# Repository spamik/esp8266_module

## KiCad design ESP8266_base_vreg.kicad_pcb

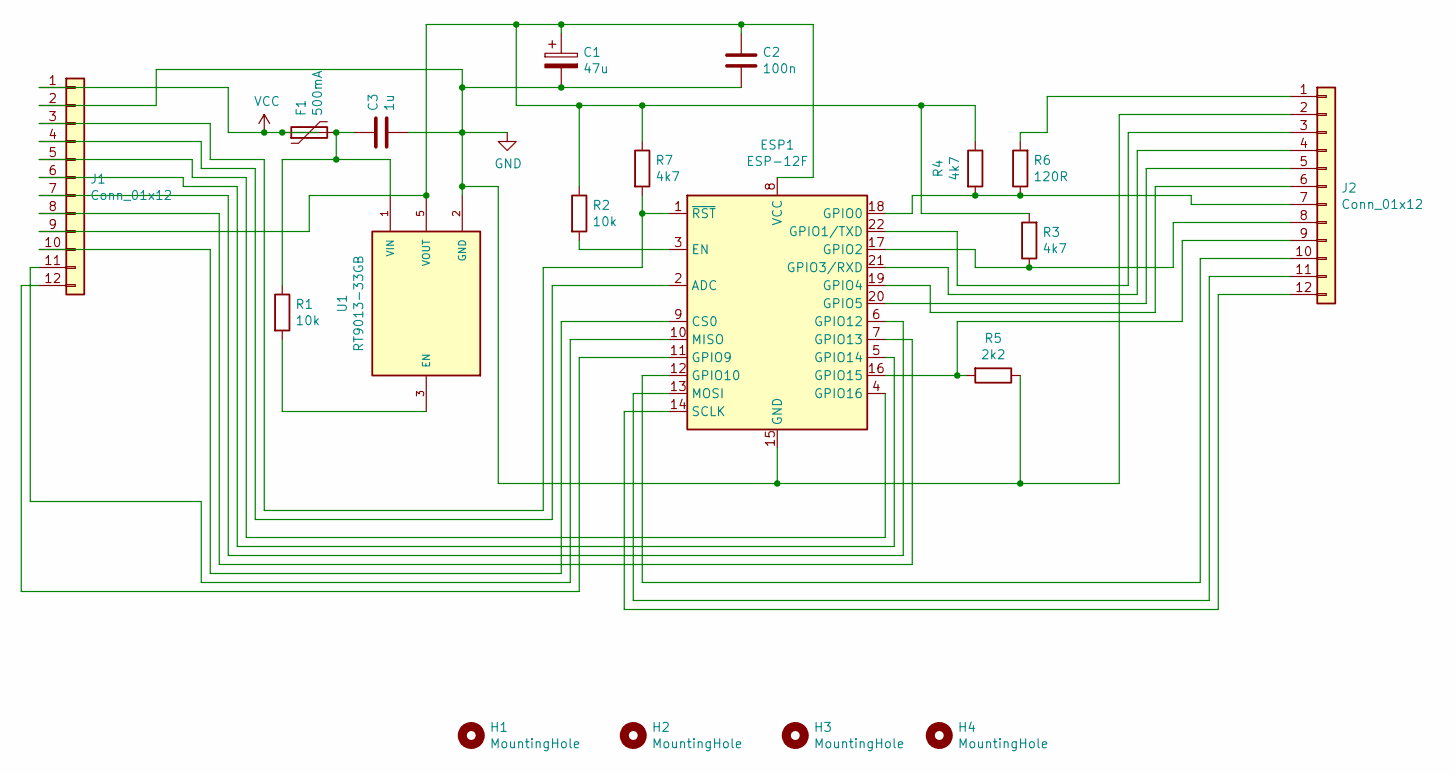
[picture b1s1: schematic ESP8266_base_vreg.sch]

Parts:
C1: 47u; CP_Elec_6.3x5.3
C2: 100n; C_0603_1608Metric_Pad1.08x0.95mm_HandSolder
C3: 1u; C_0603_1608Metric_Pad1.08x0.95mm_HandSolder
ESP1: ESP-12F; ESP-12E
F1: 500mA; Fuse_1812_4532Metric
H1, H2, H3, H4: MountingHole; MountingHole_2.7mm_M2.5
J1, J2: Conn_01x12; PinHeader_1x12_P2.54mm_Vertical
R1, R2: 10k; R_0805_2012Metric_Pad1.20x1.40mm_HandSolder
R3, R4, R7: 4k7; R_0805_2012Metric_Pad1.20x1.40mm_HandSolder
R5: 2k2; R_0805_2012Metric_Pad1.20x1.40mm_HandSolder
R6: 120R; R_0805_2012Metric_Pad1.20x1.40mm_HandSolder
U1: RT9013-33GB; SOT94P279X129-5N; PARTREV Aprill 2011

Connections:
GND: C1.2, C2.2, C3.2, ESP1.15 (GND), J1.2, J2.2, R5.1, U1.2 (GND)
unnamed: C1.1, C2.1, ESP1.8 (VCC), J1.9, R2.1, R3.2, R4.1, R7.1, U1.5 (VOUT)
unnamed: C3.1, F1.2, R1.1, U1.1 (VIN)
unnamed: ESP1.1 (~RST), J1.3, R7.2
unnamed: ESP1.2 (ADC), J1.4
unnamed: ESP1.3 (EN), R2.2
unnamed: ESP1.4 (GPIO16), J1.5
unnamed: ESP1.5 (GPIO14), J1.6
unnamed: ESP1.6 (GPIO12), J1.7
unnamed: ESP1.7 (GPIO13), J1.8
unnamed: ESP1.9 (CS0), J1.10
unnamed: ESP1.10 (MISO), J1.11
unnamed: ESP1.11 (GPIO9), J1.12
unnamed: ESP1.12 (GPIO10), J2.10
unnamed: ESP1.13 (MOSI), J2.11
unnamed: ESP1.14 (SCLK), J2.12
unnamed: ESP1.16 (GPIO15), J2.9, R5.2
unnamed: ESP1.17 (GPIO2), J2.8, R3.1
unnamed: ESP1.18 (GPIO0), J2.7, R4.2, R6.1
unnamed: ESP1.19 (GPIO4), J2.6
unnamed: ESP1.20 (GPIO5), J2.5
unnamed: ESP1.21 (GPIO3/RXD), J2.4
unnamed: ESP1.22 (GPIO1/TXD), J2.3
unnamed: J2.1, R6.2
unnamed: R1.2, U1.3 (EN)
VCC: F1.1, J1.1

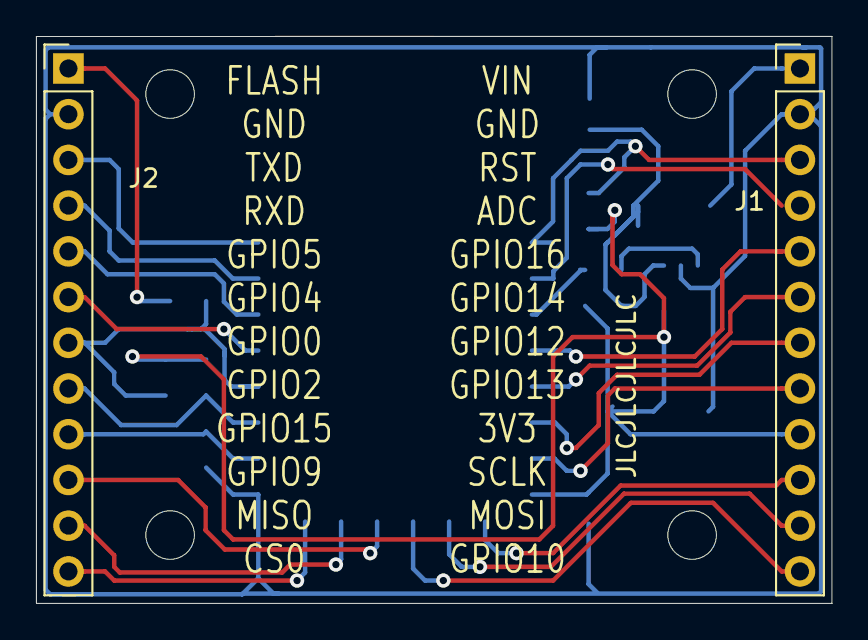
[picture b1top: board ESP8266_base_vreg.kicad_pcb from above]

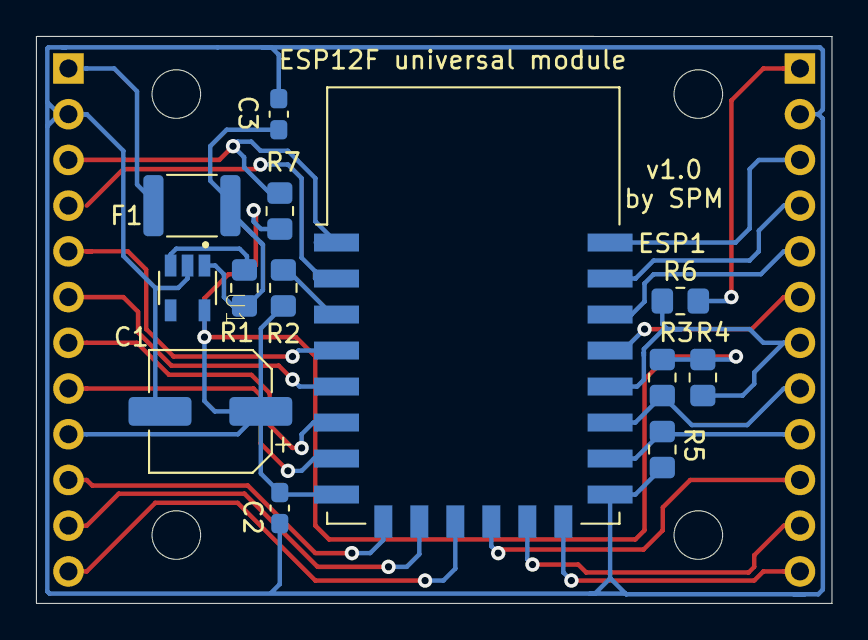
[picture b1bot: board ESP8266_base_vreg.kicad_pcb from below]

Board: 2 copper layers, 44.2 x 31.5 mm, 19 parts (13 on the bottom side), 26 nets.

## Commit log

2021-01-16 Initial import
